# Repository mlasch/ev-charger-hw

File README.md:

# EV Charger PCB

Interface to a IEC 61851-1 (AC charging) EV.

> [!NOTE]  
> The PCB is untested and should be used with cauton.

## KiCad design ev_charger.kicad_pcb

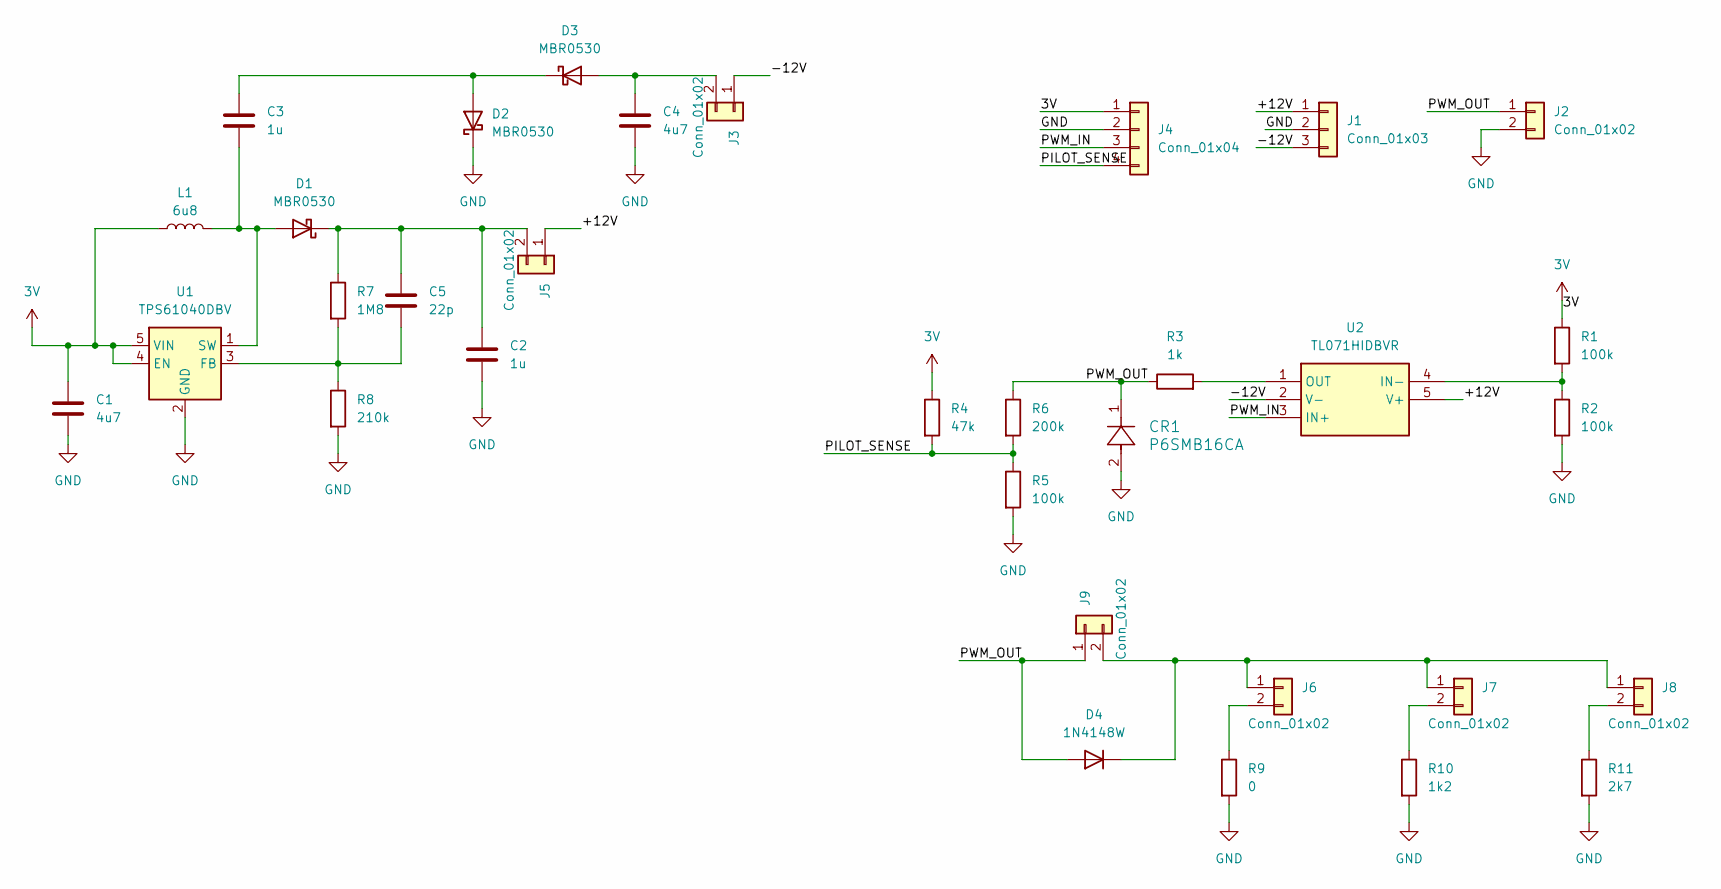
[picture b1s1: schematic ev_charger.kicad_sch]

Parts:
C1, C4: 4u7; C_0603_1608Metric; JLC 0603
C2, C3: 1u; C_0603_1608Metric; JLC 0603
C5: 22p; C_0603_1608Metric; JLC 0603
CR1: P6SMB16CA; P6SMBSeries_LTF; LCSC C80386
D1, D2, D3: MBR0530; D_SOD-123; LCSC C77336
D4: 1N4148W; D_SOD-123; JLC SOD-123
J1: Conn_01x03; PinHeader_1x03_P2.54mm_Vertical; LCSC C24980
J2, J6, J7, J8, J9: Conn_01x02; PinHeader_1x02_P2.54mm_Vertical
J3, J5: Conn_01x02; PinHeader_1x02_P2.54mm_Vertical; LCSC C703015
J4: Conn_01x04; PinHeader_1x04_P2.54mm_Vertical
L1: 6u8; L_1812_4532Metric; JLC 1812
R1, R2, R5: 100k; R_0603_1608Metric; JLC 0603
R3: 1k; R_0603_1608Metric; JLC 0603
R4: 47k; R_0603_1608Metric; JLC 0603
R6: 200k; R_0603_1608Metric; JLC 0603
R7: 1M8; R_0603_1608Metric; JLC 0603
R8: 210k; R_0603_1608Metric; JLC 0603
R9: 0; R_0603_1608Metric; JLC 0603
R10: 1k2; R_0603_1608Metric; JLC 0603
R11: 2k7; R_0603_1608Metric; JLC 0603
U1: TPS61040DBV; SOT-23-5; LCSC C7722
U2: TL071HIDBVR; SOT95P280X145-5N; Manufacturer_Part_Number TL071HIDBVR; Mouser Part Number 595-TL071HIDBVR

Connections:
3V: C1.1, J4.1, L1.1, R1.1, R4.1, U1.4 (EN), U1.5 (VIN)
/+12V: J1.1, J5.1, U2.5 (V+)
/-12V: J1.3, J3.1, U2.2 (V-)
/PILOT_SENSE: J4.4, R4.2, R5.1, R6.2
/PWM_IN: J4.3, U2.3 (IN+)
/PWM_OUT: CR1.1, D4.2 (A), J2.1, J9.1, R3.1, R6.1
GND: C1.2, C2.2, C4.2, CR1.2, D2.1 (K), J1.2, J2.2, J4.2, R2.2, R5.2, R8.2, R9.2, R10.2, R11.2, U1.2 (GND)
unnamed: C3.2, D1.2 (A), L1.2, U1.1 (SW)
unnamed: C2.1, C5.1, D1.1 (K), J5.2, R7.1
unnamed: C3.1, D2.2 (A), D3.1 (K)
unnamed: C4.1, D3.2 (A), J3.2
unnamed: D4.1 (K), J6.1, J7.1, J8.1, J9.2
unnamed: J6.2, R9.1
unnamed: J7.2, R10.1
unnamed: J8.2, R11.1
unnamed: C5.2, R7.2, R8.1, U1.3 (FB)
unnamed: R1.2, R2.1, U2.4 (IN-)
unnamed: R3.2, U2.1 (OUT)

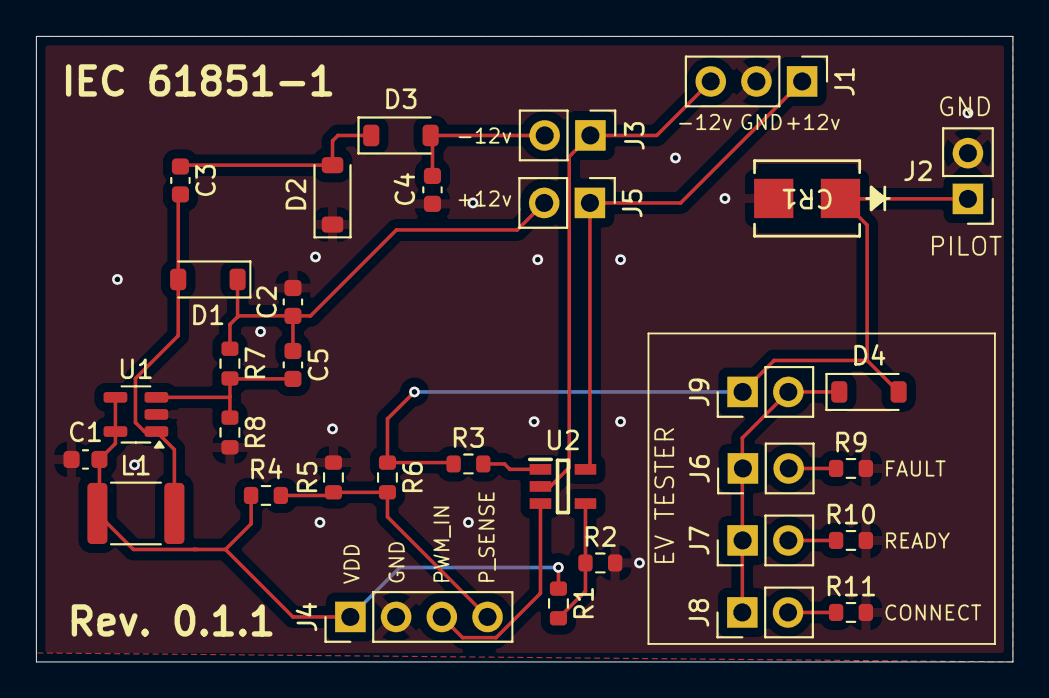
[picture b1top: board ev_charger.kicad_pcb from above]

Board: 2 copper layers, 54.2 x 34.8 mm, 33 parts (0 on the bottom side), 18 nets.

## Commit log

2026-03-01 Initial KiCad ev_charger project commit
    The initial version contains the analog interface for the pilot signal.
2026-03-01 ci: Generate PDFs for schematic and layout
2026-03-01 readme: Add
2026-03-28 Fix missing via bug
2026-03-28 Rename 3.3v to 3v/VDD
2026-03-28 Adjust resistor values
    - Change r3 to 1k to adjust output CE PWM voltage.
    - Change r4 to 46k to increase bias. This avoids negative sense
    voltages.
